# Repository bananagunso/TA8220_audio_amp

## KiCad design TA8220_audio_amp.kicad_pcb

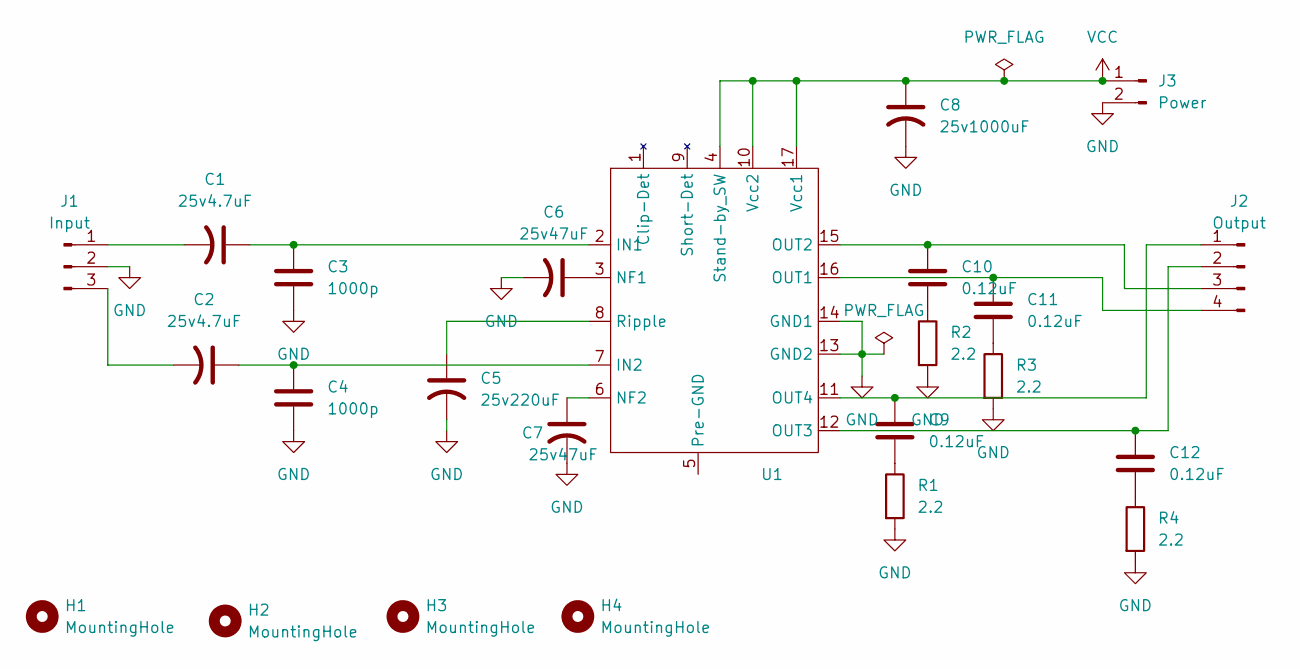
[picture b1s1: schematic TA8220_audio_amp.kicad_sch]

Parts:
C1, C2: 25v4.7uF; CP_Radial_D5.0mm_P2.50mm
C3, C4: 1000p; 5.3_2.5_p2.5
C5: 25v220uF; CP_Radial_D8.0mm_P5.00mm
C6, C7: 25v47uF; CP_Radial_D5.0mm_P2.50mm
C8: 25v1000uF; CP_Radial_D10.0mm_P5.00mm
C9, C10, C11, C12: 0.12uF; 11.6_7.0_p7.5
H1, H2, H3, H4: MountingHole; MountingHole_3.2mm_M3
J1: Input; JST_XH_B3B-XH-A_1x03_P2.50mm_Vertical
J2: Output; JST_XH_B4B-XH-A_1x04_P2.50mm_Vertical
J3: Power; JST_XH_B2B-XH-A_1x02_P2.50mm_Vertical
R1, R2, R3, R4: 2.2; R_Axial_DIN0617_L17.0mm_D6.0mm_P20.32mm_Horizontal
U1: TA-8220HQ

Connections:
GND: C3.2, C4.2, C5.2, C6.2, C7.2, C8.2, J1.2, J3.2, R1.2, R2.2, R3.2, R4.2, U1.13 (GND2), U1.14 (GND1)
unnamed: C9.2, R1.1
unnamed: C10.2, R2.1
unnamed: C11.2, R3.1
unnamed: C12.2, R4.1
unnamed: C1.2, J1.1
unnamed: C2.2, J1.3
unnamed: C9.1, J2.1, U1.11 (OUT4)
unnamed: C12.1, J2.2, U1.12 (OUT3)
unnamed: C10.1, J2.3, U1.15 (OUT2)
unnamed: C11.1, J2.4, U1.16 (OUT1)
unnamed: C1.1, C3.1, U1.2 (IN1)
unnamed: C2.1, C4.1, U1.7 (IN2)
unnamed: C6.1, U1.3 (NF1)
unnamed: C7.1, U1.6 (NF2)
unnamed: C5.1, U1.8 (Ripple)
VCC: C8.1, J3.1, U1.4 (Stand-by_SW), U1.10 (Vcc2), U1.17 (Vcc1)

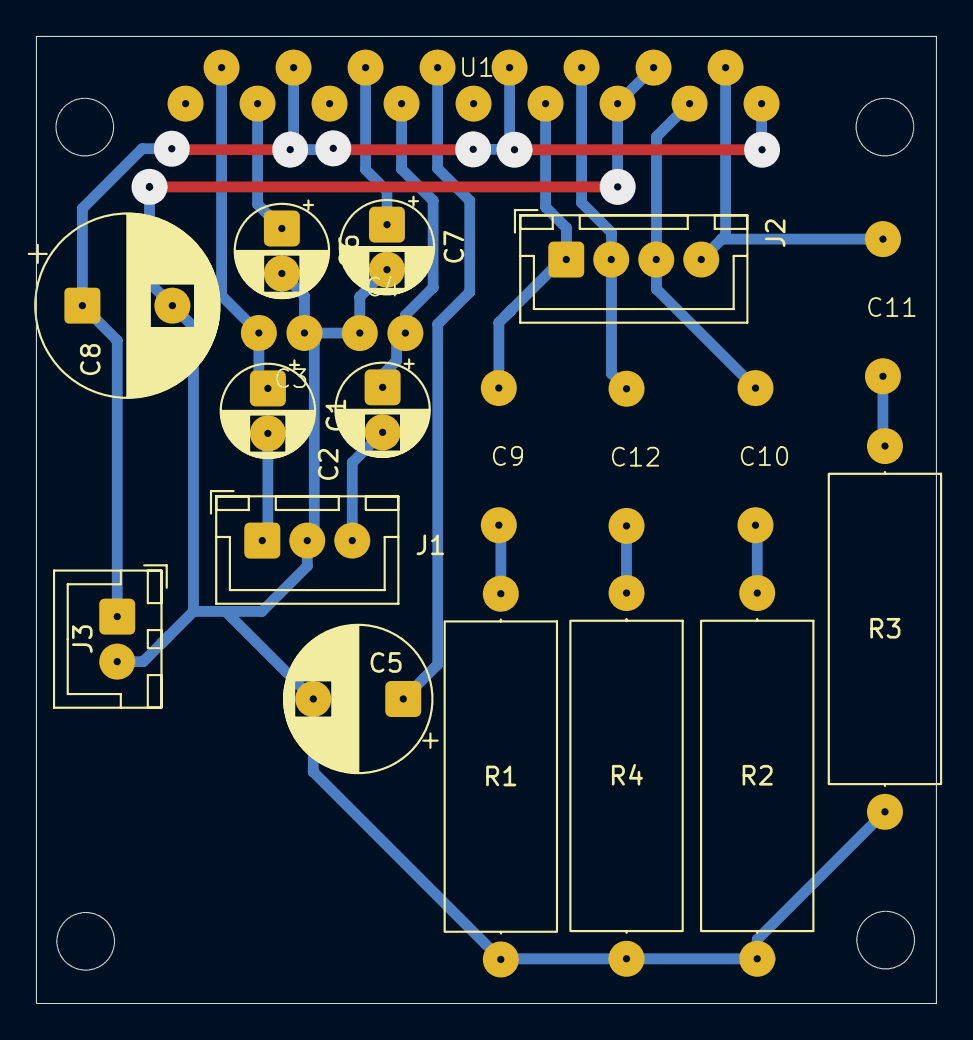
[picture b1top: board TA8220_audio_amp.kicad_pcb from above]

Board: 2 copper layers, 50.0 x 53.7 mm, 24 parts (0 on the bottom side), 17 nets.

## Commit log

2025-11-18 昔部品を買ったまま放置していたTA8220を使う
2025-11-18 シルクスクリーンを修正
2025-11-19 http://vicdiy.com/products/TV_linked_amp2/linked_amp2.html を参考に利得を下げるよう部品を変更
2025-11-21 パッド径を2に修正
2025-11-21 50mmに収めた
2025-11-24 パッド修正、ベタ追加
2025-11-24 ベタを修正
2025-11-26 ジャンパのパッドの大きさを修正
2025-11-27 C1,C2を4.7 -> 0.47に修正
2025-11-28 データシートどおりに作り直し
